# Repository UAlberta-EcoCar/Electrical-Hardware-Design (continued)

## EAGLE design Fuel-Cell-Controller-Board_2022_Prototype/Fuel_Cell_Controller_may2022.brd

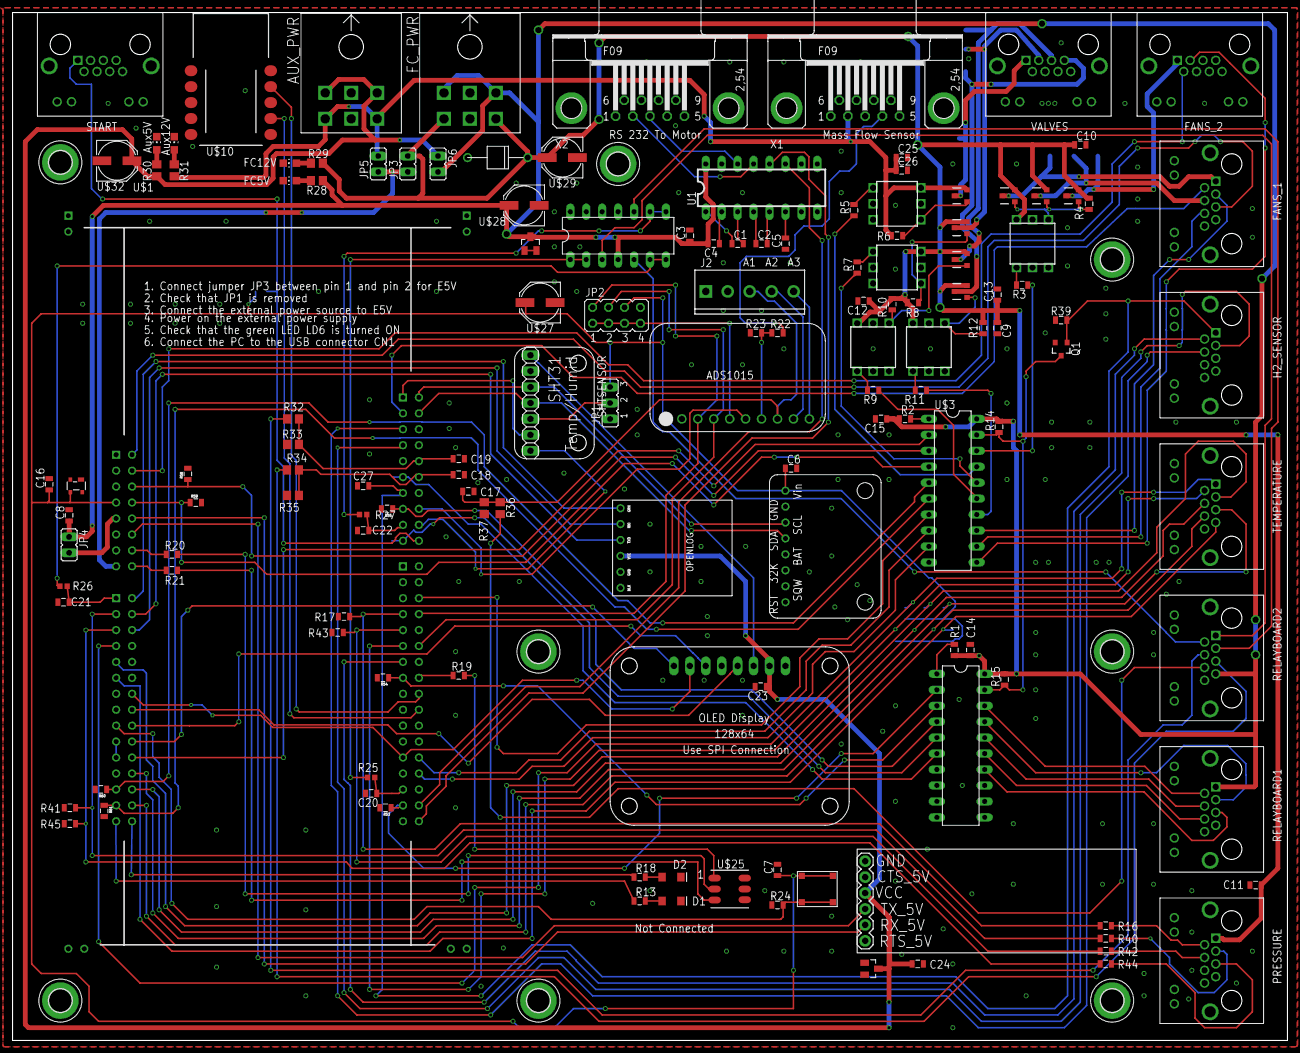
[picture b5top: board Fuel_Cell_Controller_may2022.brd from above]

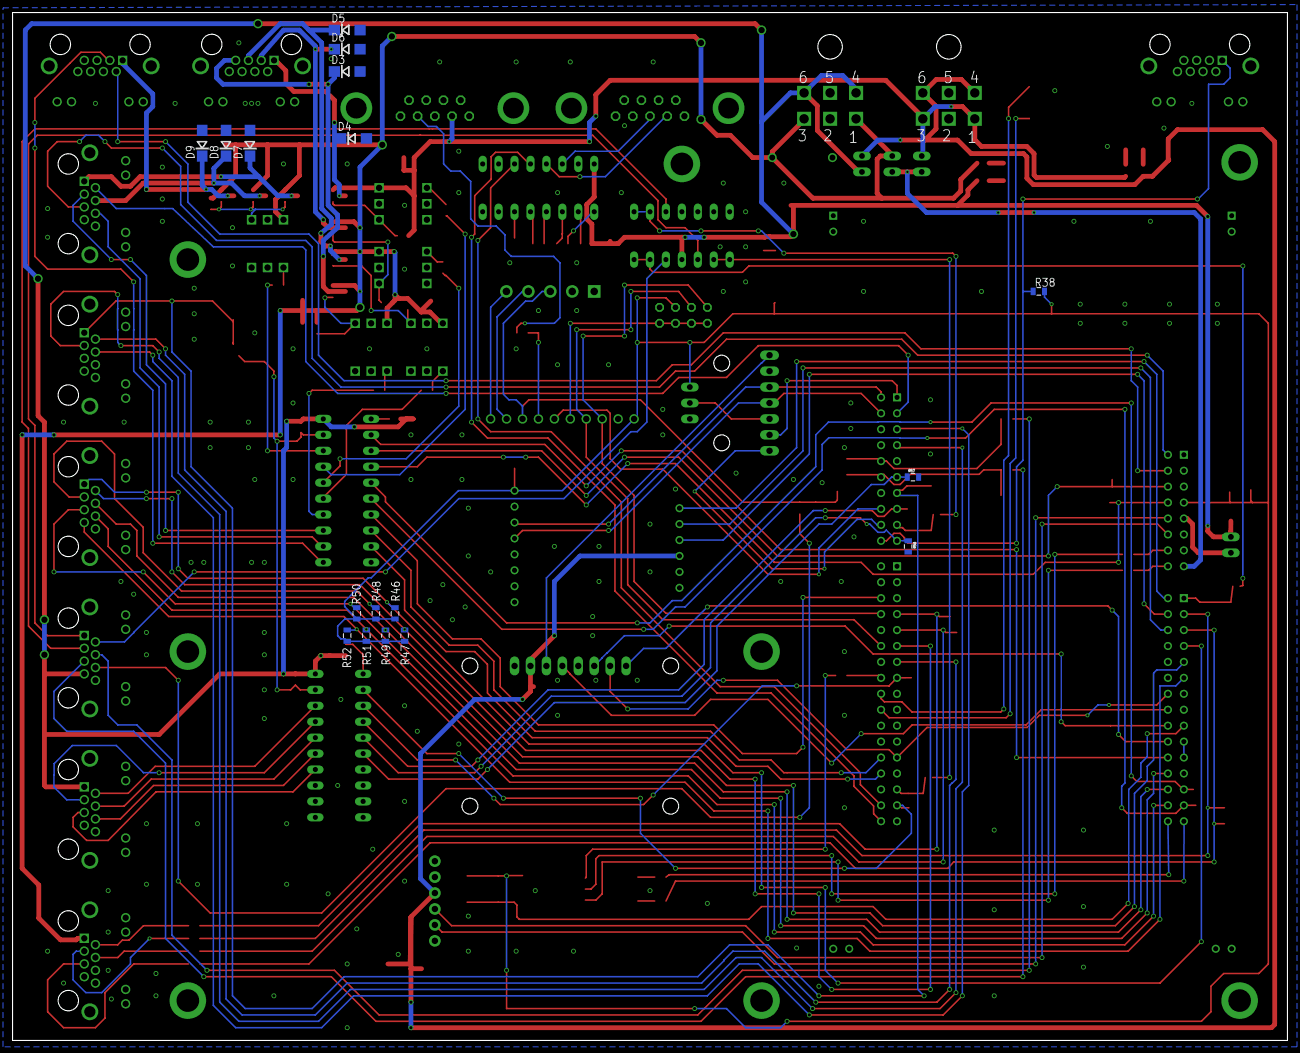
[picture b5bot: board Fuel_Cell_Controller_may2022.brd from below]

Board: 4 copper layers, 203.2 x 163.8 mm, 164 parts (17 on the bottom side), 143 nets.

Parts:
AUX5VLED, AUX12VLED: CHIP-LED0805
AUX_PWR: TE_6-PIN
C1, C2, C3, C4, C5, C8, C23, C24, C27: 1µF; 0805
C6, C7, C14, C15, C16: 0.1µF; 0805
C9, C10, C11, C12, C13, C25, C26: 10µF; 0805
C17, C18, C19, C20, C21, C22: 0805
D1: RED; LED-1206
D2: YELLOW; LED-1206
D3, D4, D5, D6, D7, D8, D9: DO214AC
FANS_1, FANS_2: ETHERNET; A122645-ND
FC5VLED, FC12VLED: CHIP-LED0805
FC_PWR: TE_6-PIN
H1, H2, H3, H4, H5, H6, H7, H8: MOUNT-PAD-ROUND3.6; 3,6-PAD
H2_SENSOR: ETHERNET; A122645-ND
J1: BLUETOOTH; 1X06BLUETOOTH
J2: SCREWTERMINAL-3.5MM-5
JP1: JP2
JP2: JP4Q
JP3, JP4, JP5, JP6: JP1
LP_FILTER_OP_AMP: TLV2404TLV2404; DIL14
PRESSURE: ETHERNET; A122645-ND
Q1: 5.8A/30V/35mΩ; SOT23-3
R1, R2, R22, R23, R38: 1kΩ; 0805
R3, R5, R7, R9, R11: 470Ω; 0805
R4, R6, R8, R10, R12, R14, R15, R16, R17, R24, R39, R40, R41, R42, R43, R44, R45, R53, R54, R55, R56, R57, R58, R59, R60, R61: 10kΩ; 0805
R13, R18, R19, R20, R21: 324Ω; 0805
R25, R26, R27: 0402
R28, R29: 604Ω; R0805
R30, R31: 324Ω; R0805
R32, R33, R34, R35, R36, R37: R0805
R46, R47, R48, R49, R50, R51, R52: 100kΩ; 0805
RELAYBOARD1, RELAYBOARD2: ETHERNET; A122645-ND
SHTSENSOR: SHT31-DIS; 1X07-SHT31-DIS
START: ETHERNET; A122645-ND
TEMPERATURE: ETHERNET; A122645-ND
U1: MAX232PTH; DIL16
U$1: NUCLEO-F746ZGNUCLEO-F746ZG; NUCLEO-F746ZG
U$2: OPENLOG
U$3, U$5: SN74LVC245AN; DIL20
U$4, U$6, U$11, U$14, U$16: H11L1H11L1; H11L1
U$7, U$8, U$9, U$12, U$13, U$15, U$17: DMP3056L-7DMP3056L-7; DMP3056L-7
U$10: UMFT234XF
U$18: DS3231
U$19: ADS1015
U$20: CD143A-SR3.3CT-ND; SOT143_AVAGO
U$21, U$31: 641-1198-1-ND; SOT23
U$22: P6KE15A-E3/54GICT-ND; DO-204AC
U$25: 5060BRG45060BRG4; 5060BRG4
U$26: EG4621CT-ND
U$27, U$28, U$32: 1µF; PANASONIC_D
U$29: 10µF; PANASONIC_D
U$30: ADAFRUITOLED; 1X08OLED
VALVES: ETHERNET; A122645-ND
X1, X2: F09HP

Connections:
ADC_A2: J2.4, U$19.P$9
ADC_A3: J2.5, U$19.P$10
ADC_ADDR: JP2.1, JP2.3, JP2.5, JP2.7, U$19.P$5
ADC_ALERT: U$1.PD_14, U$19.P$6
ALARM_LED: R13.1, U$1.PG_0
AUX3V3: SHTSENSOR.1, U$30.P$6
AUX5V: AUX_PWR.4, AUX_PWR.6, C23.1, C24.1, J1.3, JP6.1, R30.2, U$2.P$4, U$30.P$7, U$31.C, U$32.+
AUX12V: AUX_PWR.1, AUX_PWR.3, C25.1, C26.1, JP5.2, R6.1, R31.2, U$6.VCC, U$12.S, X1.2
BUTTON: R24.2, U$1.PF_2, U$26.P$3, U$26.P$4
CAP_CURR: C17.1, J2.3, R36.2, R37.1, U$19.P$8
CAP_RELAY: RELAYBOARD1.P$3, U$5.17
CAP_VOLT: LP_FILTER_OP_AMP.10, RELAYBOARD2.P$3
CHARGE_RELAY: RELAYBOARD1.P$6, U$5.15
DEBUG_LED: R18.1, U$1.PG_1
ESTOP_1: H2_SENSOR.P$3, U$1.PB_12
ESTOP_2: H2_SENSOR.P$4, U$1.PB_13
FAN1_PWR: D7.C, FANS_1.P$1, U$7.D
FAN2_PWR: D8.C, FANS_1.P$4, U$8.D
FAN3_PWR: D9.C, FANS_2.P$1, U$9.D
FANS_GATE: R4.2, U$4.VO, U$7.G, U$8.G, U$9.G
FANS_SWITCH_ALL: R3.1, U$3.18
FC5V: C3.1, C4.2, C8.1, C14.1, C15.1, FC_PWR.4, FC_PWR.6, JP4.1, JP6.2, LP_FILTER_OP_AMP.4, R1.1, R2.1, R14.2, R15.2, R28.2, RELAYBOARD1.P$1, RELAYBOARD2.P$7, U1.16, U$3.20, U$5.20, U$21.C, U$28.+
FC12V: C9.1, C10.1, C11.1, C12.1, C13.1, FC_PWR.1, FC_PWR.3, JP3.2, PRESSURE.P$1, R4.1, R8.1, R10.1, R12.1, R29.2, U$4.VCC, U$7.S, U$8.S, U$9.S, U$11.VCC, U$13.S, U$14.VCC, U$15.S, U$16.VCC, U$17.S, U$22.CATHODE, U$29.+
FCC_RELAY: RELAYBOARD1.P$2, U$5.18
FCTEMP_1: R46.2, TEMPERATURE.P$1, U$1.PF_3
FCTEMP_2: R47.2, TEMPERATURE.P$2, U$1.PF_4
FC_CURR: C19.1, R32.2, R33.1, U$1.PA_5
FC_VOLT: LP_FILTER_OP_AMP.3, RELAYBOARD2.P$1
FROM_BLUE: J1.4, U$1.PD_2
FROM_FTDI: U$1.PE_7, U$10.7
FROM_MOTOR: U1.13, X2.2
FROM_OPEN: U$1.PD_6, U$2.P$3
GND: AUX5VLED.C, AUX12VLED.C, AUX_PWR.2, AUX_PWR.5, C3.2, C5.1, C6.2, C7.2, C8.2, C9.2, C10.2, C11.2, C12.2, C13.2, C14.2, C15.2, C16.2, C17.2, C18.2, C19.2, C20.2, C21.2, C22.2, C23.2, C24.2, C25.2, C26.2, C27.2, D1.C, D2.C, D3.A, D4.A, D5.A, D6.A, D7.A, D8.A, D9.A, FANS_1.P$7, FANS_1.P$8, FANS_1.P$13, FANS_1.P$14, FANS_2.P$6, FANS_2.P$7, FANS_2.P$8, FANS_2.P$13, FANS_2.P$14, FC5VLED.C, FC12VLED.C, FC_PWR.2, FC_PWR.5, H1.B3,6, H2.B3,6, H2_SENSOR.P$5, H2_SENSOR.P$6, H2_SENSOR.P$7, H2_SENSOR.P$8, H2_SENSOR.P$13, H2_SENSOR.P$14, H3.B3,6, H4.B3,6, H5.B3,6, H6.B3,6, H7.B3,6, H8.B3,6, J1.1, J2.1, JP1.1, JP2.8, LP_FILTER_OP_AMP.11, LP_FILTER_OP_AMP.12, LP_FILTER_OP_AMP.13, PRESSURE.P$7, PRESSURE.P$8, PRESSURE.P$13, PRESSURE.P$14, Q1.2, R17.1, R23.1, R24.1, R33.2, R35.2, R37.2, R39.1, R41.1, R43.1, R45.1, R53.2, R54.2, R55.2, R56.2, R57.2, R58.2, R59.2, R60.2, R61.2, RELAYBOARD1.P$7, RELAYBOARD1.P$8, RELAYBOARD1.P$13, RELAYBOARD1.P$14, RELAYBOARD2.P$8, RELAYBOARD2.P$13, RELAYBOARD2.P$14, SHTSENSOR.2, START.P$8, START.P$13, START.P$14, TEMPERATURE.P$8, TEMPERATURE.P$13, TEMPERATURE.P$14, U1.15, U$1.AGND, U$1.GND1, U$1.GND2, U$1.GND3, U$1.GND4, U$1.GND5, U$1.GND6, U$1.GND7, U$1.GND8, U$1.GND9, U$1.GND10, U$1.GND11, U$1.GND12, U$1.GND13, U$1.GND14, U$1.GND15, U$1.GND16, U$1.GND17, U$2.P$5, U$2.P$6, U$3.10, U$4.CATHODE, U$4.GND, U$5.10, U$6.CATHODE, U$6.GND, U$10.4, U$11.CATHODE, U$11.GND, U$14.CATHODE, U$14.GND, U$16.CATHODE, U$16.GND, U$18.P$2, U$19.P$2, U$20.GND, U$21.A1, U$21.A2, U$22.ANODE, U$25.4, U$25.5, U$25.6, U$27.-, U$28.-, U$29.-, U$30.P$8, U$31.A1, U$31.A2, U$32.-, VALVES.P$2, VALVES.P$4, VALVES.P$6, VALVES.P$8, VALVES.P$13, VALVES.P$14, X1.1, X1.3, X2.5
H2_OK: H2_SENSOR.P$2, U$1.PB_6
HUMID_RST: SHTSENSOR.6, U$1.PC_6
I2C1_SCL: SHTSENSOR.3, U$1.PB_8, U$18.P$3
I2C1_SDA: SHTSENSOR.4, U$1.PB_9, U$18.P$4
I2C4_SCL: JP2.2, U$1.PF_14, U$19.P$3
I2C4_SDA: JP2.4, U$1.PF_15, U$19.P$4
INTERRUPT: U$1.PH_0, U$1.PH_1
MASS_FLOW: R22.1, R23.2, U$19.P$7
MOTOR_CURR: C18.1, R34.2, R35.1, U$1.PA_6
MOTOR_RELAY: RELAYBOARD1.P$4, U$5.16
MOTOR_RX: U1.12, U$1.PB_11
MOTOR_TX: U1.11, U$1.PB_10
MOTOR_VOLT: LP_FILTER_OP_AMP.5, RELAYBOARD2.P$2
unnamed: JP4.2, U$1.5V
unnamed: R5.2, U$6.ANODE
unnamed: C1.1, U1.1
unnamed: C1.2, U1.3
unnamed: C2.1, U1.4
unnamed: C2.2, U1.5
unnamed: C4.1, U1.2
unnamed: C5.2, U1.6
unnamed: R7.2, U$11.ANODE
unnamed: R2.2, U$3.1
unnamed: R1.2, U$5.1
unnamed: R3.2, U$4.ANODE
unnamed: R9.2, U$14.ANODE
unnamed: R11.2, U$16.ANODE
unnamed: R22.2, X1.4
unnamed: D1.A, R13.2
unnamed: D2.A, R18.2
unnamed: R19.2, U$25.1
unnamed: R20.2, U$25.2
unnamed: R21.2, U$25.3
unnamed: FC5VLED.A, R28.1
unnamed: FC12VLED.A, R29.1
unnamed: LP_FILTER_OP_AMP.1, LP_FILTER_OP_AMP.2, R25.2
unnamed: AUX5VLED.A, R30.1
unnamed: LP_FILTER_OP_AMP.6, LP_FILTER_OP_AMP.7, R26.2
unnamed: LP_FILTER_OP_AMP.8, LP_FILTER_OP_AMP.9, R27.1
unnamed: AUX12VLED.A, R31.1
NUC_3V3: C6.1, C7.1, C16.1, JP1.3, JP2.6, R38.2, R46.1, R47.1, R48.1, R49.1, R50.2, R51.2, R52.2, U$1.3V3, U$18.P$1, U$19.P$1, U$20.VDD, U$26.P$1, U$26.P$2, U$27.+
OE*: Q1.3, R14.1, R15.1, U$3.19, U$5.19
OLED_CLK: U$1.PE_2A, U$1.PE_2B, U$30.P$2
OLED_MISO: U$1.PE_5, U$30.P$3
OLED_MOSI: U$1.PE_6, U$30.P$1
OLED_SEL: U$1.PE_4, U$30.P$5
OPEN_RST: U$1.PD_7, U$2.P$1
OUTPUT_1: R9.1, U$3.15
OUTPUT_1_ENET: D5.C, U$15.D, VALVES.P$5
OUTPUT_1_GATE: R10.2, U$14.VO, U$15.G
OUTPUT_2: R11.1, U$3.14
OUTPUT_2_ENET: D3.C, U$17.D, VALVES.P$7
OUTPUT_2_GATE: R12.2, U$16.VO, U$17.G
PRESSURE_1: R16.1, R17.2, U$1.PB_1
PRESSURE_2: R40.1, R41.2, U$1.PC_0
PRESSURE_3: R42.1, R43.2, U$1.PC_2
PRESSURE_4: R44.1, R45.2, U$1.PC_3
PURGE_VALVE: R7.1, U$3.16
PURGE_VALVE_ENET: D6.C, U$13.D, VALVES.P$3
PURGE_VALVE_GATE: R8.2, U$11.VO, U$13.G
PWM_1: FANS_1.P$3, U$3.13
PWM_2: FANS_1.P$6, U$3.12
PWM_3: FANS_2.P$3, U$3.11
RUN_LED: R19.1, U$1.PG_9
SHT31_ALERT: SHTSENSOR.7, U$1.PD_15
SHT_ADR: JP1.2, SHTSENSOR.5
SHUT_LED: R20.1, U$1.PG_2
START_LED: R21.1, U$1.PG_3
START_RELAY: RELAYBOARD1.P$5, U$5.14
STOP: C27.1, H2_SENSOR.P$1, Q1.1, R39.2, U$1.PB_5
SUPPLY_VALVE: R5.1, U$3.17
SUPPLY_VALVE_ENET: D4.C, U$12.D, VALVES.P$1
SUPPLY_VALVE_GATE: R6.2, U$6.VO, U$12.G
TACH_1: FANS_1.P$2, U$1.PB_15
TACH_2: FANS_1.P$5, U$1.PC_8
TACH_3: FANS_2.P$2, U$1.PC_9
TEMP_1: R48.2, TEMPERATURE.P$3, U$1.PF_5
TEMP_2: R49.2, TEMPERATURE.P$4, U$1.PF_7
TEMP_3: R50.1, TEMPERATURE.P$5, U$1.PF_8
TEMP_4: R51.1, TEMPERATURE.P$6, U$1.PF_9
TEMP_5: R52.1, TEMPERATURE.P$7, U$1.PF_10
TO_BLUE: J1.5, U$1.PC_12
TO_FTDI: U$1.PE_8, U$10.9
TO_MOTOR: U1.14, X2.3
TO_OPEN: U$1.PD_5, U$2.P$2
VIN: JP3.1, JP5.1, U$1.VIN
_CAP_CURR: R36.1, RELAYBOARD2.P$6
_CAP_RELAY: R54.1, U$1.PB_2, U$5.3
_CAP_VOLT: C22.1, R27.2, U$1.PA_4
_CHARGE_RELAY: R56.1, U$1.PB_4, U$5.5
_FANS_SWITCH_ALL: U$1.PE_3, U$3.2
_FCC_RELAY: R53.1, U$1.PB_0, U$5.2
_FC_CURR: R32.1, RELAYBOARD2.P$4
_FC_VOLT: C20.1, R25.1, U$1.PA_0
_MOTOR_CURR: R34.1, RELAYBOARD2.P$5
_MOTOR_RELAY: R55.1, U$1.PB_3, U$5.4
_MOTOR_VOLT: C21.1, R26.1, U$1.PA_3
_OUTPUT_1: R60.1, U$1.PD_0, U$3.5
_OUTPUT_2: R61.1, U$1.PD_1, U$3.6
_PRESSURE_1: PRESSURE.P$2, R16.2
_PRESSURE_2: PRESSURE.P$3, R40.2
_PRESSURE_3: PRESSURE.P$4, R42.2
_PRESSURE_4: PRESSURE.P$5, R44.2
_PURGE_VALVE: R59.1, U$1.PC_11, U$3.4
_PWM_1: U$1.PE_11, U$3.7
_PWM_2: U$1.PE_12, U$3.8
_PWM_3: U$1.PE_14, U$3.9
_START: R38.1, START.P$1, U$1.PF_12
_START_RELAY: R57.1, U$1.PC_7, U$5.6
_SUPPLY_VALVE: R58.1, U$1.PC_10, U$3.3

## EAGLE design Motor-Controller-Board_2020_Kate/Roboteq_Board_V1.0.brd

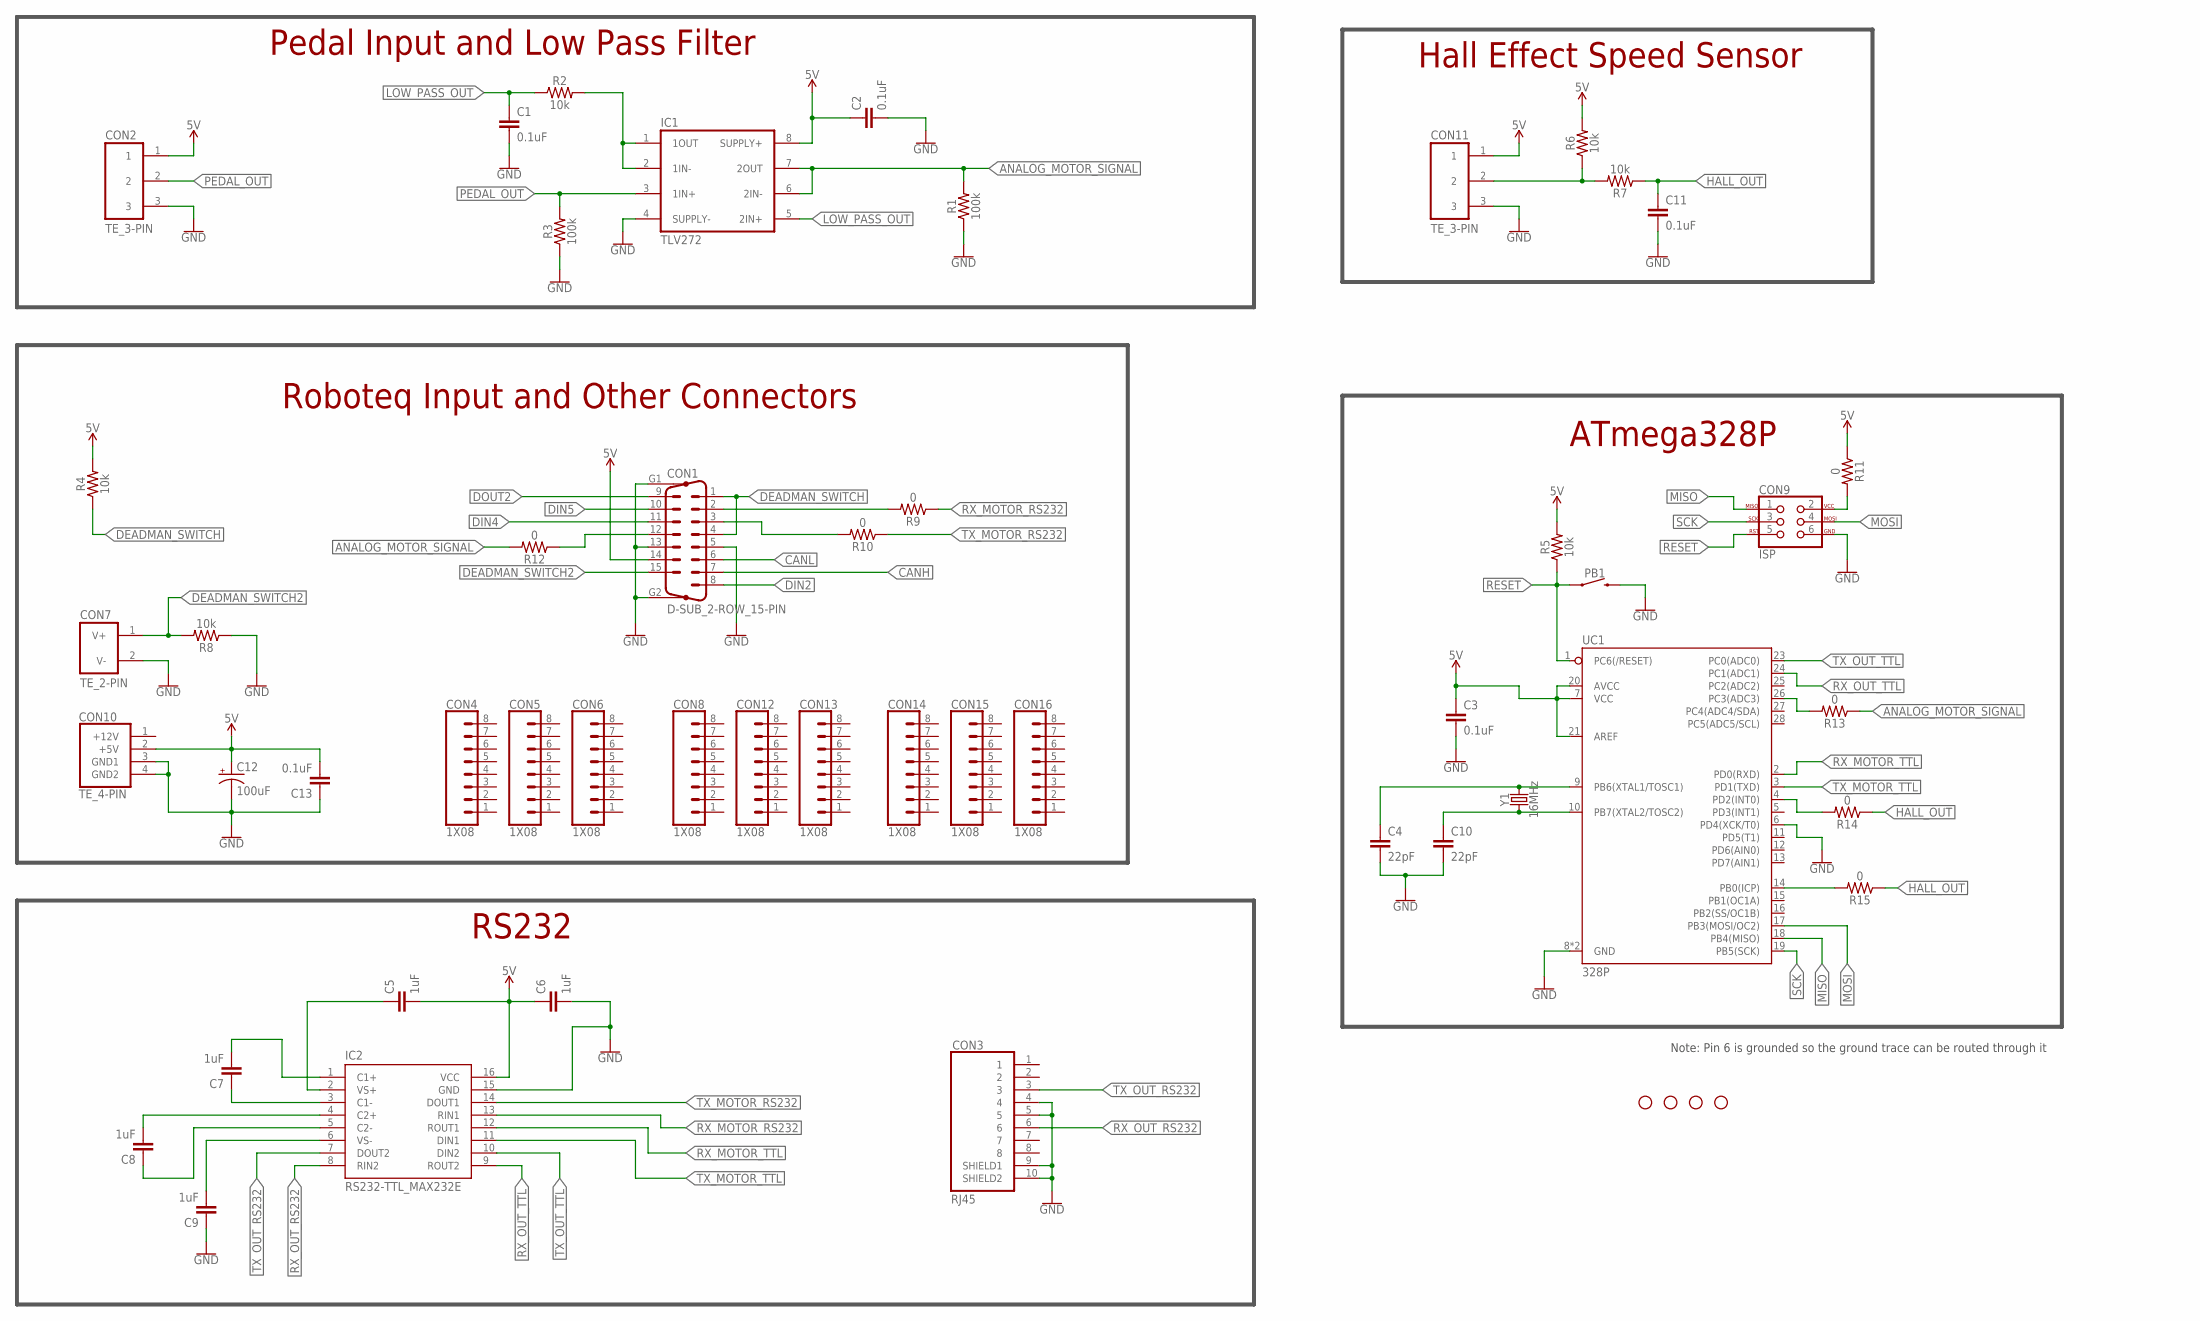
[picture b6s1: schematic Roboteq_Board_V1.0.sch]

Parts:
C1, C2, C3, C11, C13: 0.1uF; CAP-PTH-5MM
C4, C10: 22pF; CAP-PTH-5MM
C5, C6, C7, C8, C9: 1uF; CAP-PTH-5MM
C12: 100uF; CAPACITOR_100UF_50V
CON1: D-SUB_2-ROW_15-PIN
CON2, CON11: TE_3-PIN
CON3: RJ45
CON4, CON5, CON6, CON8, CON12, CON13, CON14, CON15, CON16: 1X08
CON7: TE_2-PIN
CON9: ISP; ISP_CONNECTOR
CON10: TE_4-PIN
H1, H2, H3, H4: STAND-OFF
IC1: TLV272; DIP08
IC2: RS232-TTL_MAX232E; DIP16
PB1: PUSHBUTTON
R1, R3: 100k; AXIAL-0.3
R2, R4, R5, R6, R7, R8: 10k; AXIAL-0.3
R9, R10, R11, R12, R13, R14, R15: 0; AXIAL-0.3
UC1: 328P; DIP28
Y1: 16MHz; HC49US

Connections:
5V: C2.1, C3.1, C5.2, C6.1, C12.+, C13.2, CON1.14, CON2.1, CON10.2 (+5V), CON11.1, IC1.8 (SUPPLY+), IC2.16 (VCC), R4.P$2 (2), R5.P$2 (2), R6.P$2 (2), R11.P$1 (1), UC1.7 (VCC), UC1.20 (AVCC), UC1.21 (AREF)
ANALOG_MOTOR_SIGNAL: IC1.6 (2IN-), IC1.7 (2OUT), R1.P$2 (2), R12.P$2 (2), R13.P$1 (1)
CANH: CON1.7
CANL: CON1.6
DEADMAN_SWITCH: CON1.1, CON1.4, R4.P$1 (1)
DEADMAN_SWITCH2: CON1.15, CON7.1 (V+), R8.P$2 (2)
DIN2: CON1.8
DIN4: CON1.11
DIN5: CON1.10
DOUT2: CON1.9
GND: C1.2, C2.2, C3.2, C4.2, C6.2, C9.1, C10.2, C11.2, C12.-, C13.1, CON1.5, CON1.13, CON1.G1 (GND1), CON1.G2 (GND2), CON2.3, CON3.4, CON3.5, CON3.9 (SHIELD1), CON3.10 (SHIELD2), CON7.2 (V-), CON9.6, CON10.3 (GND1), CON10.4 (GND2), CON11.3, IC1.4 (SUPPLY-), IC2.15 (GND), PB1.3 (2), PB1.4 (2), R1.P$1 (1), R3.P$1 (1), R8.P$1 (1), UC1.6 (PD4(XCK/T0)), UC1.8 (GND), UC1.22 (GND)
HALL_OUT: C11.1, R7.P$1 (1), R14.P$1 (1), R15.P$1 (1)
LOW_PASS_OUT: C1.1, IC1.5 (2IN+), R2.P$1 (1)
MISO: CON9.1, UC1.18 (PB4(MISO))
MOSI: CON9.4, UC1.17 (PB3(MOSI/OC2))
unnamed: CON1.2, R9.P$2 (2)
unnamed: IC1.1 (1OUT), IC1.2 (1IN-), R2.P$2 (2)
unnamed: R13.P$2 (2), UC1.26 (PC3(ADC3))
unnamed: C4.1, UC1.9 (PB6(XTAL1/TOSC1)), Y1.2
unnamed: C10.1, UC1.10 (PB7(XTAL2/TOSC2)), Y1.1
unnamed: C7.2, IC2.1 (C1+)
unnamed: C5.1, IC2.2 (VS+)
unnamed: C7.1, IC2.3 (C1-)
unnamed: C8.2, IC2.4 (C2+)
unnamed: C8.1, IC2.5 (C2-)
unnamed: C9.2, IC2.6 (VS-)
unnamed: CON11.2, R6.P$1 (1), R7.P$2 (2)
unnamed: CON1.3, R10.P$2 (2)
unnamed: CON9.2, R11.P$2 (2)
unnamed: CON1.12, R12.P$1 (1)
unnamed: R14.P$2 (2), UC1.4 (PD2(INT0))
unnamed: R15.P$2 (2), UC1.14 (PB0(ICP))
PEDAL_OUT: CON2.2, IC1.3 (1IN+), R3.P$2 (2)
RESET: CON9.5, PB1.1, PB1.2 (1), R5.P$1 (1), UC1.1 (PC6(/RESET))
RX_MOTOR_RS232: IC2.13 (RIN1), R9.P$1 (1)
RX_MOTOR_TTL: IC2.12 (ROUT1), UC1.2 (PD0(RXD))
RX_OUT_RS232: CON3.6, IC2.8 (RIN2)
RX_OUT_TTL: IC2.9 (ROUT2), UC1.24 (PC1(ADC1))
SCK: CON9.3, UC1.19 (PB5(SCK))
TX_MOTOR_RS232: IC2.14 (DOUT1), R10.P$1 (1)
TX_MOTOR_TTL: IC2.11 (DIN1), UC1.3 (PD1(TXD))
TX_OUT_RS232: CON3.3, IC2.7 (DOUT2)
TX_OUT_TTL: IC2.10 (DIN2), UC1.23 (PC0(ADC0))

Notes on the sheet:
Hall Effect Speed Sensor
Pedal Input and Low Pass Filter
RS232
ATmega328P
Roboteq Input and Other Connectors
Note: Pin 6 is grounded so the ground trace can be routed through it

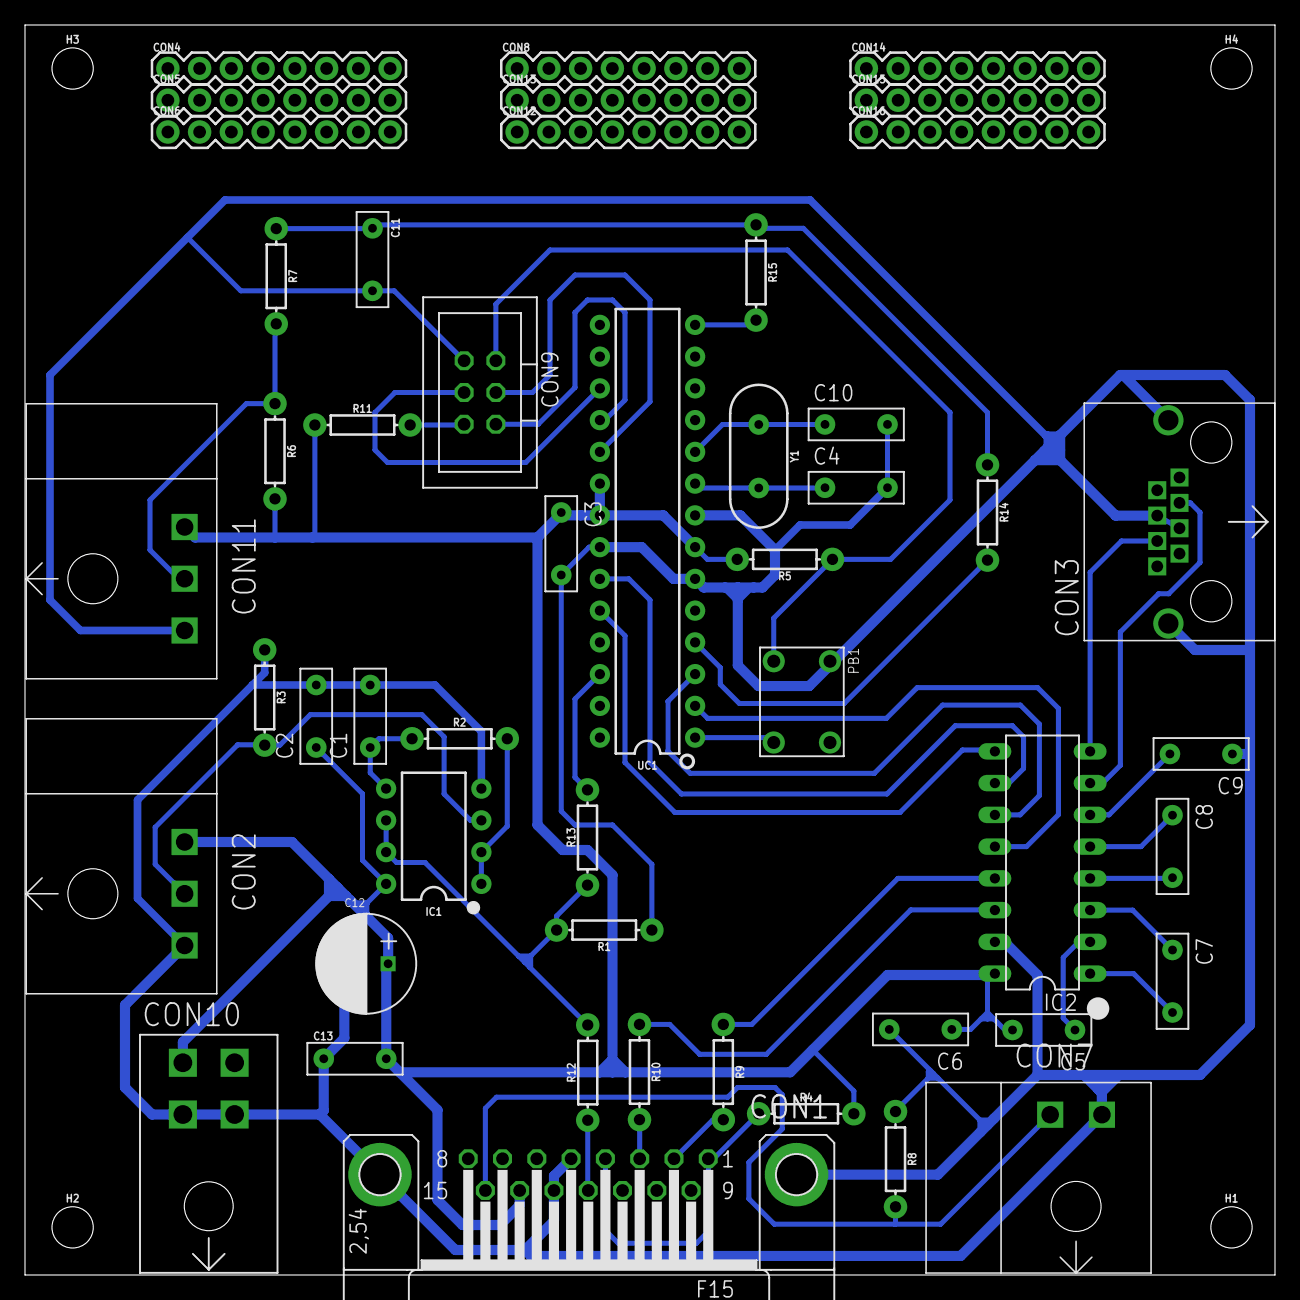
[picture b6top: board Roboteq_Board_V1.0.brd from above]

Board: 2 copper layers, 100.0 x 100.0 mm, 53 parts (0 on the bottom side), 37 nets.
